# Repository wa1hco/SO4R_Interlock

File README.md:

# SO4R_Interlock V2
The interlock manages up to 4 radios for a contesting scenario

Baseline capability for one SSB/CW radio plus 3 WSJTX radios.
Isolation is sufficient to allow reception on three radios when one radio is transmitting.
SSB/CW radio usually has a rotatable antenna. The three WSJTx instances have radio and antenna, usually a fixed direction.  
Amplifier is shared among radios.

WSJTX feeds N1MM, Gridtracker or other program that display a combined list of stations needed from three radios.
Operator clicks on a station in the list and that WSJTX begins the contact.
SSB/CW operator can continue to operate, which interrupts WSJTX transmission.

Each of 4 radios have a priority with SSB/CW being highest.
SSB/CW operation can continue while WSJTX is making contacts while staying within the ARRL VHF contest rules because WSJTX transmission is interrupted when SSB/CW transmits.

When a higher priority tranmitter needs to interrupt a lower priority tranmission, 
the interlock gates the PTT line to the lower priority radio.  This keeps the radio's
built in sequencer operating to protect the amplifier, preamp, and relays.  
The interlock also controls the RF relays to disconnect the lower priority transmitter 
and connect the highest priority transmitter

Radio Interface
* PTT, output open collector, low true, 60V, 300 mA
* KEY, input, open collector, low true, 5 to 15 V
* CAT, bidirectional, open collector, ttl levels, serial communication
* Spare, direct connection to MCU I/O pin

Relay interface
* Relay output are drive high from nominal 12V source
  * Uses BTS5200-4 driver chip for fault protection and diagnositc capability
* 12V is sourced from a rig interface using a standard coaxial type M connector
* Each output drives dual 4:1 mux boards with added relay for isolation

USB serial interface
* Implemented with FTDI FT230 usb serial chip
* RTS, output, for signaling Transmit, connected to radio PTT
* CTS, input, available, interfaced to MCU, no function assigned
* Serial TxD, RxD, for CAT, optional growth provision
* FT230 USB EEPROM changed to make it easier to find the ports when connected to a computer
  * Manufacturer string is "FTDI WA1HCO"
  * Product string is "FT230X SO4R Port {1-4}"

SSB/CW radio interface
* highest priority radio, Priority = 1
* USB serial TxD, RxD used for MCU programming
* USB serial RTS used for keying radio from N1MM
* KEY signal from Radio used to set priority and control relays

WSJTX radio interface
* Lower priority radios, Priority = 2, 3, or 4
* USB serial implements COM port, control signal RTS used by WSJTX software
* Serial data TxD and RxD converted to CAT bidirectional open collector, growth provision
* RTS signal used for PTT command to radio
* CTS signal routed to MCU but not assigned a function

WSJTX operation
* Operator uses ssb/cw radio for contacts and has highest priority for transmitting.
* 3 WSJTX instances listen on 3 radios in 3 directions.
* Each WSJTX sends it list of callsigns to N1MM or Gridtracker which displays list of stations color coded by log status (needed or duplicate).
* The operator clicks on a callsign in the list to start a WSJTX contact.
* WSJTX indicates need to transmit by asserting RTS on its serial interface

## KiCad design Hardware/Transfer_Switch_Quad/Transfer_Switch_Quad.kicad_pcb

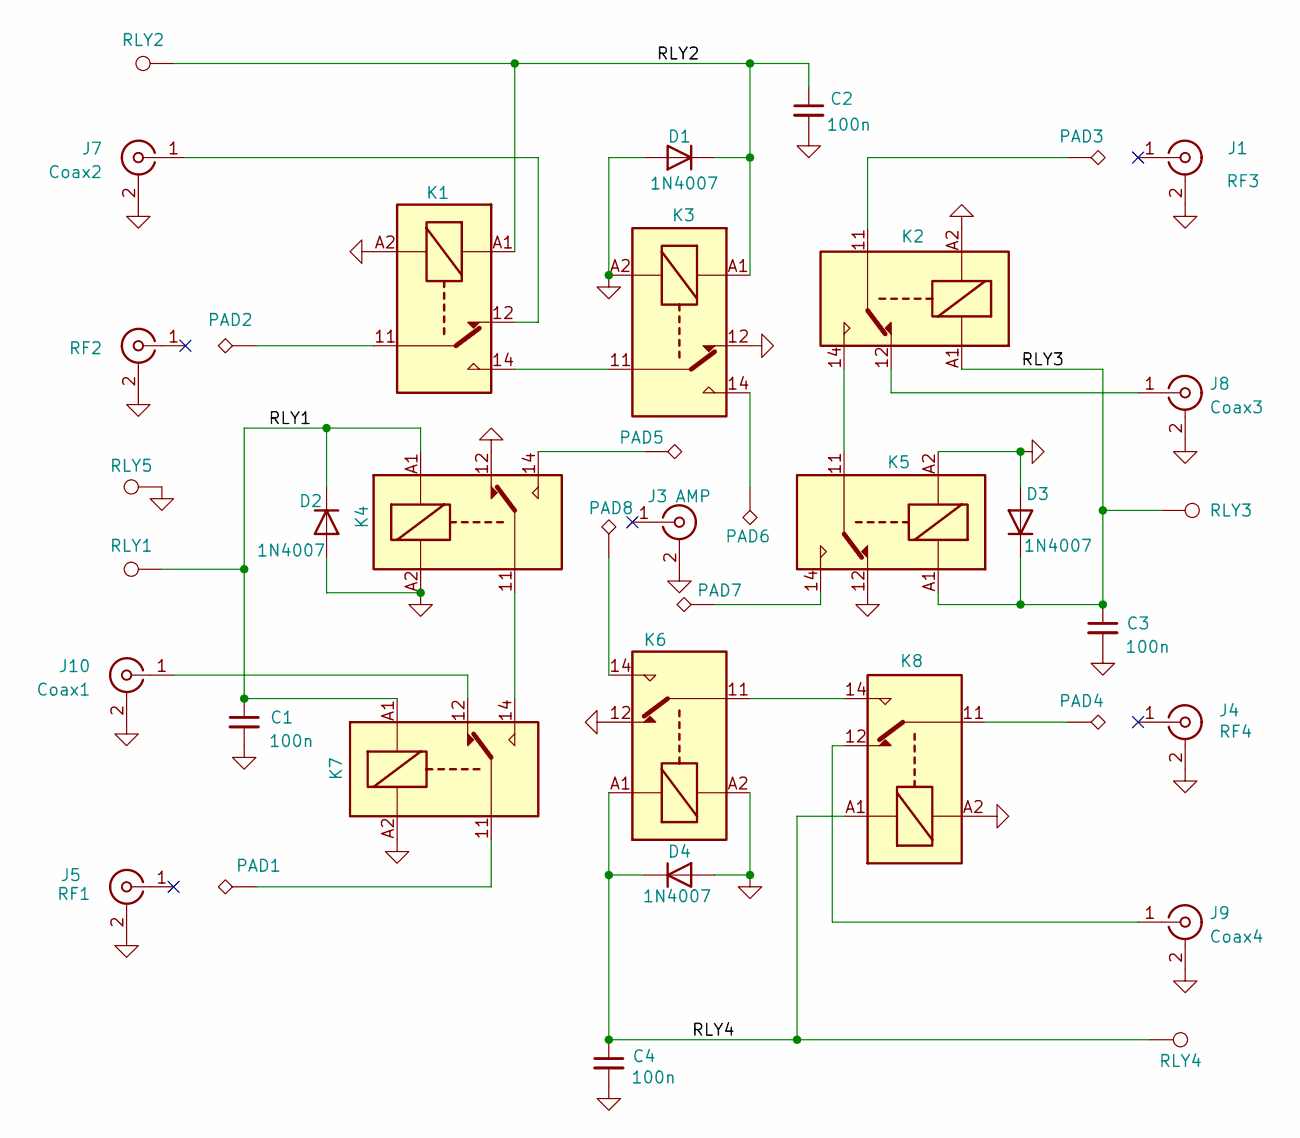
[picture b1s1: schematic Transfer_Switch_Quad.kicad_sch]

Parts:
C1, C2, C3, C4: 100n; C_0805_2012Metric
D1, D2, D3, D4: 1N4007; D_SMA
J1: RF3; UHF_SO-239_hole
J2: RF2; UHF_SO-239_hole
J3: AMP; UHF_SO-239_hole
J4: RF4; UHF_SO-239_hole
J5: RF1; UHF_SO-239_hole
J7: Coax2; SMA_Amphenol_901-144_Vertical
J8: Coax3; SMA_Amphenol_901-144_Vertical
J9: Coax4; SMA_Amphenol_901-144_Vertical
J10: Coax1; SMA_Amphenol_901-144_Vertical
K1, K2, K3, K4, K5, K6, K7, K8: G2RL-1-E; Relay_SPDT_Omron_G2RL-1-E
PAD1, PAD2, PAD3, PAD4, PAD5, PAD6, PAD7, PAD8: PAD2X4; SolderWirePad_1x01_SMD_2x4mm
RLY1, RLY2, RLY3, RLY4, RLY5: SolderWire-0.25sqmm_1x01_D0.65mm_OD2mm

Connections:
/RLY1: C1.1, D2.1 (K), K4.A1, K7.A1, RLY1.1
/RLY2: C2.1, D1.1 (K), K1.A1, K3.A1, RLY2.1
/RLY3: C3.1, D3.1 (K), K2.A1, K5.A1, RLY3.1
/RLY4: C4.1, D4.1 (K), K6.A1, K8.A1, RLY4.1
GND: C1.2, C2.2, C3.2, C4.2, D1.2 (A), D2.2 (A), D3.2 (A), D4.2 (A), J1.2 (Ext), J2.2 (Ext), J3.2 (Ext), J4.2 (Ext), J5.2 (Ext), J7.2 (Ext), J8.2 (Ext), J9.2 (Ext), J10.2 (Ext), K1.A2, K2.A2, K3.12, K3.A2, K4.12, K4.A2, K5.12, K5.A2, K6.12, K6.A2, K7.A2, K8.A2, RLY5.1
unnamed: J7.1 (In), K1.12
unnamed: J8.1 (In), K2.12
unnamed: J9.1 (In), K8.12
unnamed: J10.1 (In), K7.12
unnamed: K1.11, PAD2.1
unnamed: K1.14, K3.11
unnamed: K2.11, PAD3.1
unnamed: K2.14, K5.11
unnamed: K3.14, PAD6.1
unnamed: K4.11, K7.14
unnamed: K4.14, PAD5.1
unnamed: K5.14, PAD7.1
unnamed: K6.11, K8.14
unnamed: K6.14, PAD8.1
unnamed: K7.11, PAD1.1
unnamed: K8.11, PAD4.1

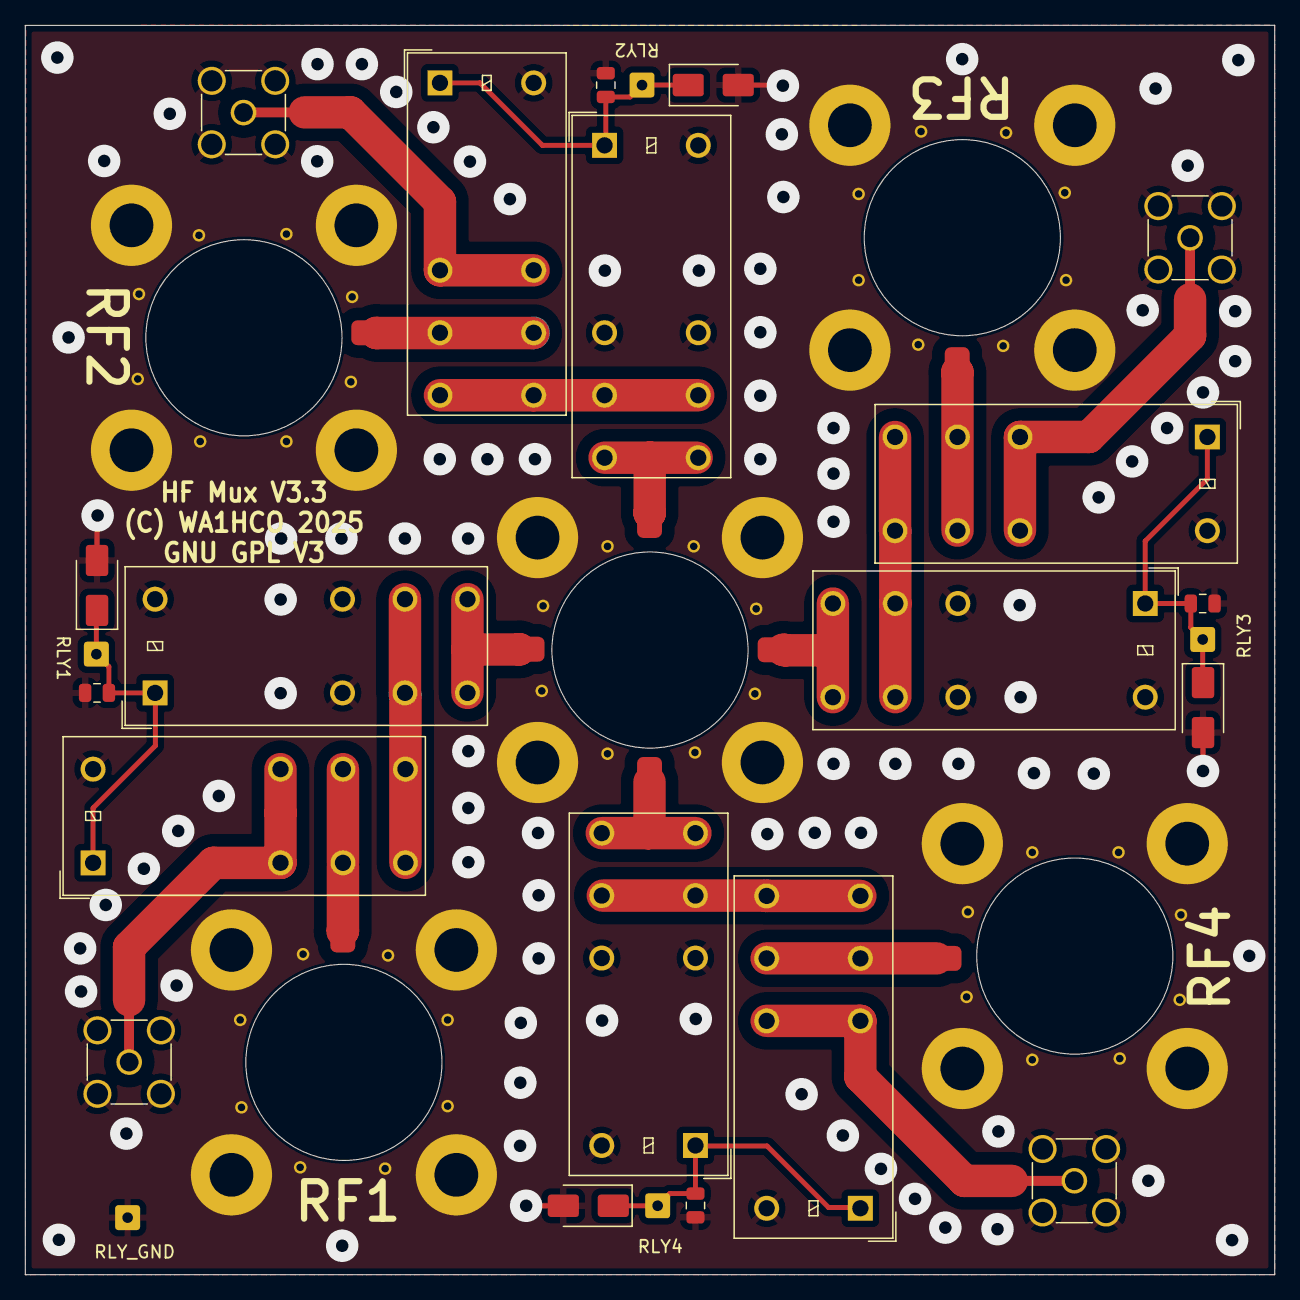
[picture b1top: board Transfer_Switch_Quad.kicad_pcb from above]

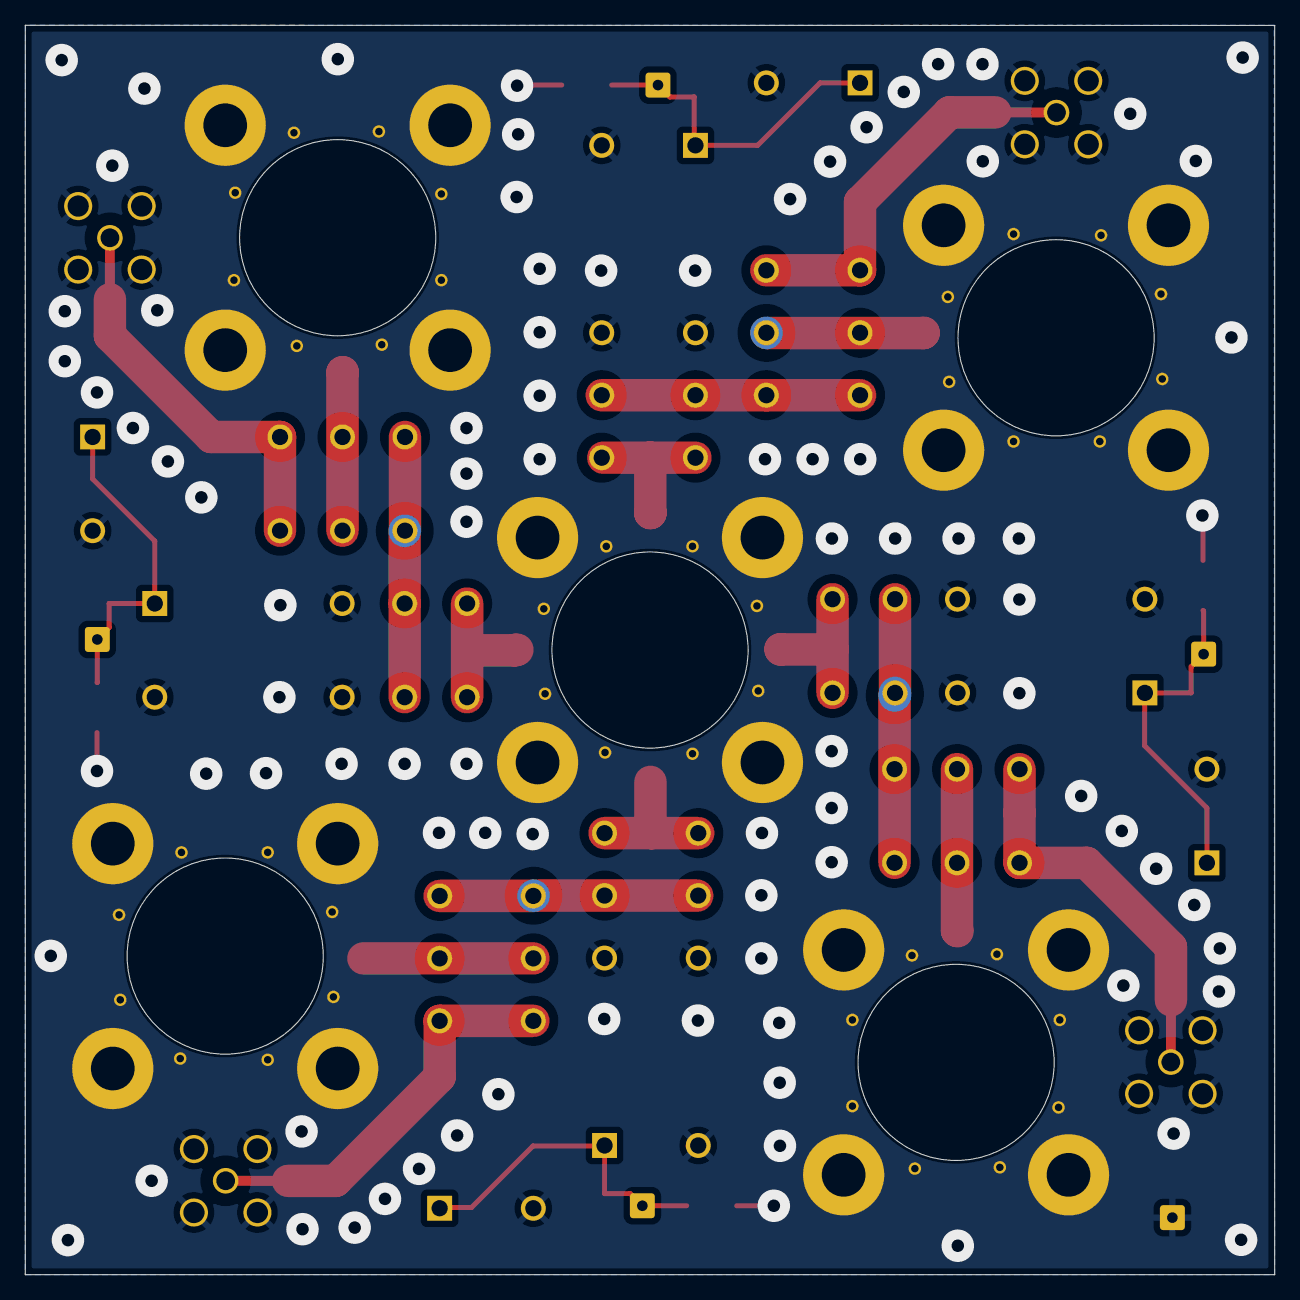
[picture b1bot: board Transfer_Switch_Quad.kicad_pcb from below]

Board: 2 copper layers, 100.0 x 100.0 mm, 38 parts (5 on the bottom side), 21 nets.

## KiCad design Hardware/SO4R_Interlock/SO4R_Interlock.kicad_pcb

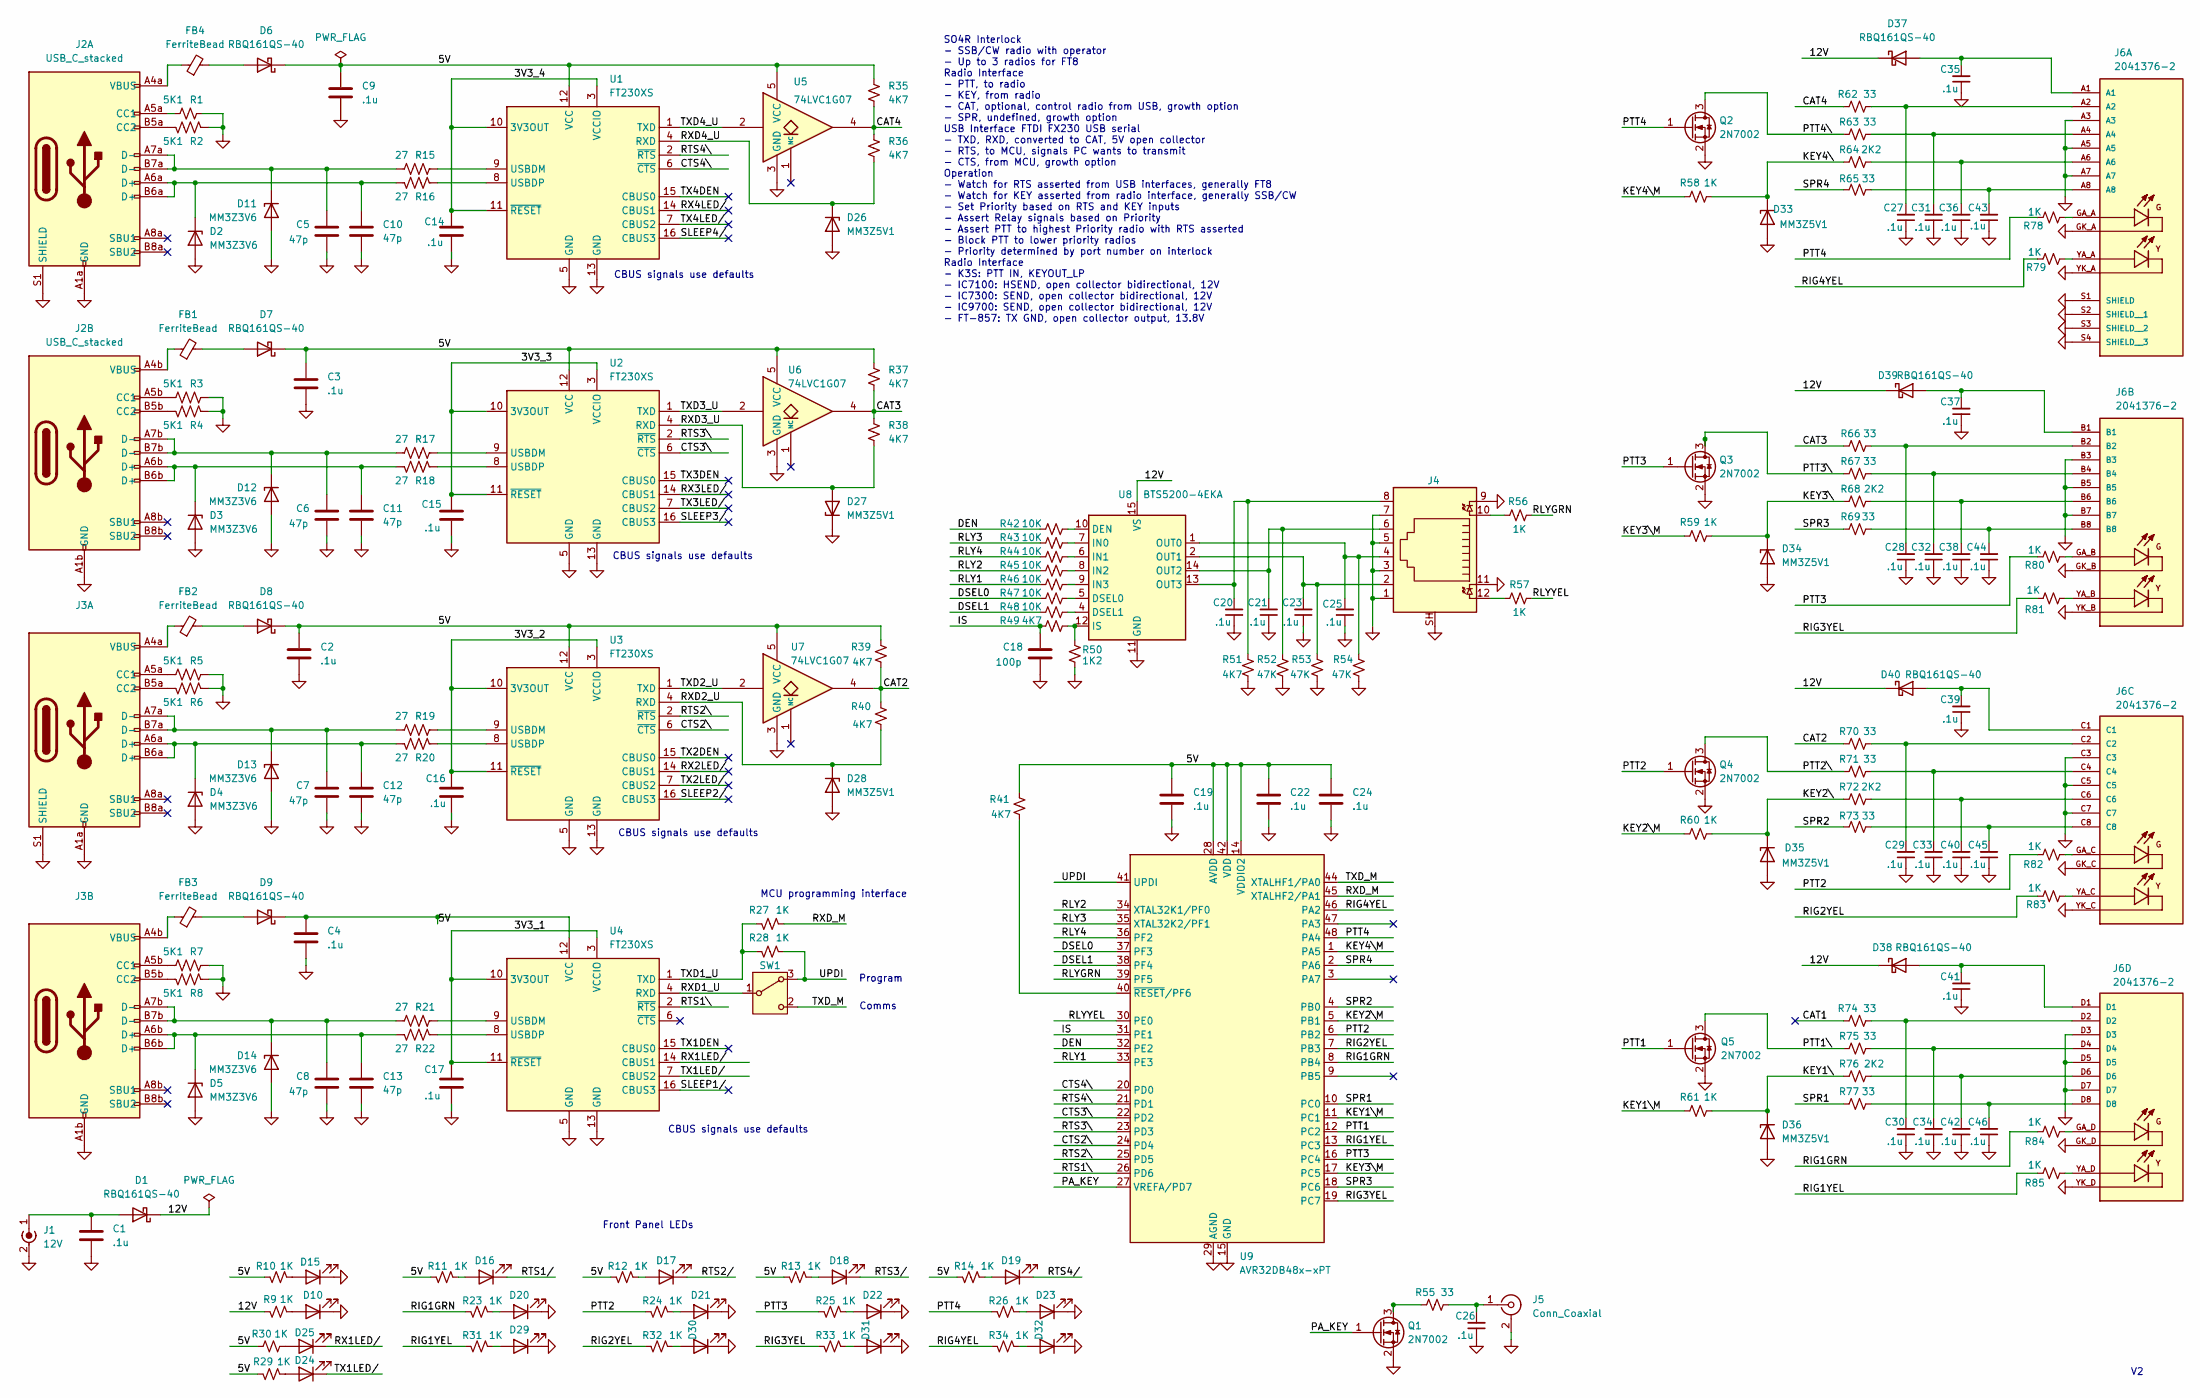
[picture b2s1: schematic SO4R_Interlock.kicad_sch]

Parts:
C1, C2, C3, C4, C9, C14, C15, C16, C17, C19, C22, C24: .1u; C_0402_1005Metric; LCSC PN C15849
C5, C6, C7, C8, C10, C11, C12, C13: 47p; C_0402_1005Metric; LCSC PN C1671
C18: 100p; C_0402_1005Metric; LCSC PN C1671
C20, C21, C23, C25, C26, C27, C28, C29, C30, C31, C32, C33, C34, C35, C36, C37, C38, C39, C40, C41, C42, C43, C44, C45, C46: .1u; C_0402_1005Metric
D1, D6, D7, D8, D9, D37, D38, D39, D40: RBQ161QS-40; D_0402_1005Metric
D2, D3, D4, D5, D11, D12, D13, D14: MM3Z3V6; D_SOD-523; LCSC PN C19077454
D10, D15: Green; LED_0603_1608Metric; LCSC PN C22371299
D16, D17, D18, D19, D20, D21, D22, D23, D29, D30, D31, D32: Green; LED_0805_2012Metric; LCSC PN C22371299
D24, D25: Yellow; LED_0603_1608Metric; LCSC PN C72038
D26, D27, D28: MM3Z5V1; D_SOD-323F
D33, D34, D35, D36: MM3Z5V1; D_SOD-523; LCSC C116949
FB1, FB2, FB3, FB4: FerriteBead; L_0805_2012Metric; LCSC PN C1017
J1: 12V; BarrelJack_Kycon_KLDX-0202-xC_Horizontal
J2: USB_C_stacked; CU3616SASCLA004-LF
J3: CU3616SASCLA004-LF
J4: RJ45_LED_Shielded; RJ45_Amphenol_RJHSE538X
J5: Conn_Coaxial; KLPX-0848A-2-B_KYC
J6: 2041376-2; TE_2041376-2; PARTREV B
Q1, Q2, Q3, Q4, Q5: 2N7002; SOT-23
R1, R2, R3, R4, R5, R6, R7, R8: 5K1; R_0402_1005Metric; LCSC PN C23186
R9, R10, R11, R12, R13, R14, R23, R24, R25, R26, R27, R28, R29, R30, R31, R32, R33, R34: 1K; R_0402_1005Metric; LCSC PN C21190
R15, R16, R17, R18, R19, R20, R21, R22: 27; R_0402_1005Metric; LCSC PN C25190
R35, R36, R37, R38, R39, R40, R41, R49, R51: 4K7; R_0402_1005Metric
R42, R43, R44, R45, R46, R47, R48: 10K; R_0402_1005Metric
R50: 1K2; R_0402_1005Metric
R52, R53, R54: 47K; R_0402_1005Metric
R55, R62, R63, R65, R66, R67, R69, R70, R71, R73, R74, R75, R77: 33; R_0402_1005Metric
R56, R57, R78, R79, R80, R81, R82, R83, R84, R85: 1K; R_0402_1005Metric
R58, R59, R60, R61: 1K; R_0402_1005Metric; LCSC C21190
R64, R68, R72, R76: 2K2; R_0402_1005Metric; LCSC C113303
SW1: SW_Wuerth_450301014042; SW_Slide-03_Wuerth-WS-SLTV_10x2.5x6.4_P2.54mm
U1, U2, U3, U4: FT230XS; SSOP-16_3.9x4.9mm_P0.635mm; LCSC PN C69082
U5, U6, U7: 74LVC1G07; SOT-23-5
U8: BTS5200-4EKA; Infineon_PG-DSO-14-48
U9: AVR32DB48x-xPT; TQFP-48_7x7mm_P0.5mm

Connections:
/3V3_1: C17.1, U4.3 (VCCIO), U4.10 (3V3OUT), U4.11 (~RESET)
/3V3_2: C16.1, U3.3 (VCCIO), U3.10 (3V3OUT), U3.11 (~RESET)
/3V3_3: C15.1, U2.3 (VCCIO), U2.10 (3V3OUT), U2.11 (~RESET)
/3V3_4: C14.1, U1.3 (VCCIO), U1.10 (3V3OUT), U1.11 (~RESET)
/5V: C2.1, C3.1, C4.1, C9.1, C19.1, C22.1, C24.1, D6.1 (K), D7.1 (K), D8.1 (K), D9.1 (K), R10.2, R11.1, R12.1, R13.1, R14.1, R29.2, R30.2, R35.1, R37.1, R39.1, R41.1, U1.12 (VCC), U2.12 (VCC), U3.12 (VCC), U4.12 (VCC), U5.5 (VCC), U6.5 (VCC), U7.5 (VCC), U9.14 (VDDIO2), U9.28 (AVDD), U9.42 (VDD)
/12V: D1.1 (K), D37.1 (K), D38.1 (K), D39.1 (K), D40.1 (K), R9.2, U8.15 (VS)
/CAT1: R74.1
/CAT2: R39.2, R40.1, R70.1, U7.4
/CAT3: R37.2, R38.1, R66.1, U6.4
/CAT4: R35.2, R36.1, R62.1, U5.4
/CTS2\: U3.6 (~CTS), U9.24 (PD4)
/CTS3\: U2.6 (~CTS), U9.22 (PD2)
/CTS4\: U1.6 (~CTS), U9.20 (PD0)
/DEN: R42.1, U9.32 (PE2)
/DSEL0: R47.1, U9.37 (PF3)
/DSEL1: R48.1, U9.38 (PF4)
/IS: C18.1, R49.1, U9.31 (PE1)
/KEY1\: D36.1 (K), R61.1, R76.2
/KEY1\M: R61.2, U9.11 (PC1)
/KEY2\: D35.1 (K), R60.1, R72.2
/KEY2\M: R60.2, U9.5 (PB1)
/KEY3\: D34.1 (K), R59.1, R68.2
/KEY3\M: R59.2, U9.17 (PC5)
/KEY4\: D33.1 (K), R58.1, R64.2
/KEY4\M: R58.2, U9.1 (PA5)
/PA_KEY: Q1.1 (G), U9.27 (VREFA/PD7)
/PTT1: Q5.1 (G), U9.12 (PC2)
/PTT1\: Q5.3 (D), R75.1
/PTT2: Q4.1 (G), R24.1, R82.2, U9.6 (PB2)
/PTT2\: Q4.3 (D), R71.1
/PTT3: Q3.1 (G), R25.1, R80.2, U9.16 (PC4)
/PTT3\: Q3.3 (D), R67.1
/PTT4: Q2.1 (G), R26.1, R78.2, U9.48 (PA4)
/PTT4\: Q2.3 (D), R63.1
/RIG1GRN: R23.1, R84.2, U9.8 (PB4)
/RIG1YEL: R31.1, R85.2, U9.13 (PC3)
/RIG2YEL: R32.1, R83.2, U9.7 (PB3)
/RIG3YEL: R33.1, R81.2, U9.19 (PC7)
/RIG4YEL: R34.1, R79.2, U9.46 (PA2)
/RLY1: R46.1, U9.33 (PE3)
/RLY2: R45.1, U9.34 (XTAL32K1/PF0)
/RLY3: R43.1, U9.35 (XTAL32K2/PF1)
/RLY4: R44.1, U9.36 (PF2)
/RLYGRN: R56.2, U9.39 (PF5)
/RLYYEL: R57.2, U9.30 (PE0)
/RTS1\: U4.2 (~RTS), U9.26 (PD6)
/RTS1/: D16.1 (K)
/RTS2\: U3.2 (~RTS), U9.25 (PD5)
/RTS2/: D17.1 (K)
/RTS3\: U2.2 (~RTS), U9.23 (PD3)
/RTS3/: D18.1 (K)
/RTS4\: U1.2 (~RTS), U9.21 (PD1)
/RTS4/: D19.1 (K)
/RX1LED/: D25.1 (K), U4.14 (CBUS1)
/RX2LED/: U3.14 (CBUS1)
/RX3LED/: U2.14 (CBUS1)
/RX4LED/: U1.14 (CBUS1)
/RXD1_U: SW1.1 (B), U4.4 (RXD)
/RXD2_U: D28.1 (K), R40.2, U3.4 (RXD)
/RXD3_U: D27.2 (A), R38.2, U2.4 (RXD)
/RXD4_U: D26.1 (K), R36.2, U1.4 (RXD)
/RXD_M: R27.2, U9.45 (XTALHF2/PA1)
/SLEEP1/: U4.16 (CBUS3)
/SLEEP2/: U3.16 (CBUS3)
/SLEEP3/: U2.16 (CBUS3)
/SLEEP4/: U1.16 (CBUS3)
/SPR1: R77.1, U9.10 (PC0)
/SPR2: R73.1, U9.4 (PB0)
/SPR3: R69.1, U9.18 (PC6)
/SPR4: R65.1, U9.2 (PA6)
/TX1DEN: U4.15 (CBUS0)
/TX1LED/: D24.1 (K), U4.7 (CBUS2)
/TX2DEN: U3.15 (CBUS0)
/TX2LED/: U3.7 (CBUS2)
/TX3DEN: U2.15 (CBUS0)
/TX3LED/: U2.7 (CBUS2)
/TX4DEN: U1.15 (CBUS0)
/TX4LED/: U1.7 (CBUS2)
/TXD1_U: R27.1, R28.1, U4.1 (TXD)
/TXD2_U: U3.1 (TXD), U7.2
/TXD3_U: U2.1 (TXD), U6.2
/TXD4_U: U1.1 (TXD), U5.2
/TXD_M: SW1.2 (C), U9.44 (XTALHF1/PA0)
/UPDI: R28.2, SW1.3 (A), U9.41 (UPDI)
GND: C1.2, C2.2, C3.2, C4.2, C5.2, C6.2, C7.2, C8.2, C9.2, C10.2, C11.2, C12.2, C13.2, C14.2, C15.2, C16.2, C17.2, C18.2, C19.2, C20.1, C21.1, C22.2, C23.1, C24.2, C25.1, C26.1, C27.1, C28.1, C29.1, C30.1, C31.1, C32.1, C33.1, C34.1, C35.1, C36.1, C37.1, C38.1, C39.1, C40.1, C41.1, C42.1, C43.1, C44.1, C45.1, C46.1, D2.2 (A), D3.2 (A), D4.2 (A), D5.2 (A), D10.1 (K), D11.2 (A), D12.2 (A), D13.2 (A), D14.2 (A), D15.1 (K), D20.1 (K), D21.1 (K), D22.1 (K), D23.1 (K), D26.2 (A), D27.1 (K), D28.2 (A), D29.1 (K), D30.1 (K), D31.1 (K), D32.1 (K), D33.2 (A), D34.2 (A), D35.2 (A), D36.2 (A), J1.2 (Ext), J2.A1a (GND), J2.A1b (GND), J2.A12a (GND), J2.A12b (GND), J2.B1a (GND), J2.B1b (GND), J2.B12a (GND), J2.B12b (GND), J2.S1 (SHIELD), J3.A1a (GND), J3.A1b (GND), J3.A12a (GND), J3.A12b (GND), J3.B1a (GND), J3.B1b (GND), J3.B12a (GND), J3.B12b (GND), J3.S1 (SHIELD), J4.1, J4.3, J4.5, J4.7, J4.9, J4.11, J4.SH, J5.2 (Ext), J6.A3, J6.A5, J6.A7, J6.B3, J6.B5, J6.B7, J6.C3, J6.C5, J6.C7, J6.D3, J6.D5, J6.D7, J6.GK_A, J6.GK_B, J6.GK_C, J6.GK_D, J6.S1 (SHIELD), J6.S2 (SHIELD__1), J6.S3 (SHIELD__2), J6.S4 (SHIELD__3), J6.YK_A, J6.YK_B, J6.YK_C, J6.YK_D, Q1.2 (S), Q2.2 (S), Q3.2 (S), Q4.2 (S), Q5.2 (S), R1.1, R2.1, R3.1, R4.1, R5.1, R6.1, R7.1, R8.1, R50.2, R51.2, R52.2, R53.2, R54.2, U1.5 (GND), U1.13 (GND), U2.5 (GND), U2.13 (GND), U3.5 (GND), U3.13 (GND), U4.5 (GND), U4.13 (GND), U5.3 (GND), U6.3 (GND), U7.3 (GND), U8.11 (GND), U9.15 (GND), U9.29 (AGND), U9.43 (GND)
unnamed: C27.2, J6.A2, R62.2
unnamed: C28.2, J6.B2, R66.2
unnamed: C29.2, J6.C2, R70.2
unnamed: C30.2, J6.D2, R74.2
unnamed: C31.2, J6.A4, R63.2
unnamed: C32.2, J6.B4, R67.2
unnamed: C33.2, J6.C4, R71.2
unnamed: C34.2, J6.D4, R75.2
unnamed: C36.2, J6.A6, R64.1
unnamed: C38.2, J6.B6, R68.1
unnamed: C40.2, J6.C6, R72.1
unnamed: C42.2, J6.D6, R76.1
unnamed: C43.2, J6.A8, R65.2
unnamed: C44.2, J6.B8, R69.2
unnamed: C45.2, J6.C8, R73.2
unnamed: C46.2, J6.D8, R77.2
unnamed: C1.1, D1.2 (A), J1.1 (In)
unnamed: C10.1, D2.1 (K), J2.A6a (D+), J2.B6a (D+), R16.2
unnamed: C11.1, D3.1 (K), J2.A6b (D+), J2.B6b (D+), R18.2
unnamed: C12.1, D4.1 (K), J3.A6a (D+), J3.B6a (D+), R20.2
unnamed: C13.1, D5.1 (K), J3.A6b (D+), J3.B6b (D+), R22.2
unnamed: D6.2 (A), FB4.2
unnamed: D7.2 (A), FB1.2
unnamed: D8.2 (A), FB2.2
unnamed: D9.2 (A), FB3.2
unnamed: D10.2 (A), R9.1
unnamed: C5.1, D11.1 (K), J2.A7a (D-), J2.B7a (D-), R15.2
unnamed: C6.1, D12.1 (K), J2.A7b (D-), J2.B7b (D-), R17.2
unnamed: C7.1, D13.1 (K), J3.A7a (D-), J3.B7a (D-), R19.2
unnamed: C8.1, D14.1 (K), J3.A7b (D-), J3.B7b (D-), R21.2
unnamed: D15.2 (A), R10.1
unnamed: D16.2 (A), R11.2
unnamed: D17.2 (A), R12.2
unnamed: D18.2 (A), R13.2
unnamed: D19.2 (A), R14.2
unnamed: D20.2 (A), R23.2
unnamed: D21.2 (A), R24.2
unnamed: D22.2 (A), R25.2
unnamed: D23.2 (A), R26.2
unnamed: D24.2 (A), R29.1
unnamed: D25.2 (A), R30.1
unnamed: D29.2 (A), R31.2
unnamed: D30.2 (A), R32.2
unnamed: D31.2 (A), R33.2
unnamed: D32.2 (A), R34.2
unnamed: C35.2, D37.2 (A), J6.A1
unnamed: C41.2, D38.2 (A), J6.D1
unnamed: C37.2, D39.2 (A), J6.B1
unnamed: C39.2, D40.2 (A), J6.C1
unnamed: FB1.1, J2.A4b (VBUS), J2.A9b (VBUS), J2.B4b (VBUS), J2.B9b (VBUS)
unnamed: FB2.1, J3.A4a (VBUS), J3.A9a (VBUS), J3.B4a (VBUS), J3.B9a (VBUS)
unnamed: FB3.1, J3.A4b (VBUS), J3.A9b (VBUS), J3.B4b (VBUS), J3.B9b (VBUS)
unnamed: FB4.1, J2.A4a (VBUS), J2.A9a (VBUS), J2.B4a (VBUS), J2.B9a (VBUS)
unnamed: J2.A5a (CC1), R1.2
unnamed: J2.B5a (CC2), R2.2
unnamed: J2.A5b (CC1), R3.2
unnamed: J2.B5b (CC2), R4.2
unnamed: J3.A5a (CC1), R5.2
unnamed: J3.B5a (CC2), R6.2
unnamed: J3.A5b (CC1), R7.2
unnamed: J3.B5b (CC2), R8.2
unnamed: J4.10, R56.1
unnamed: J4.12, R57.1
unnamed: C26.2, J5.1 (In), R55.2
unnamed: J6.GA_A, R78.1
unnamed: J6.GA_B, R80.1
unnamed: J6.GA_C, R82.1
unnamed: J6.GA_D, R84.1
unnamed: J6.YA_A, R79.1
unnamed: J6.YA_B, R81.1
unnamed: J6.YA_C, R83.1
unnamed: J6.YA_D, R85.1
unnamed: Q1.3 (D), R55.1
unnamed: R15.1, U1.9 (USBDM)
unnamed: R16.1, U1.8 (USBDP)
unnamed: R17.1, U2.9 (USBDM)
unnamed: R18.1, U2.8 (USBDP)
unnamed: R19.1, U3.9 (USBDM)
unnamed: R20.1, U3.8 (USBDP)
unnamed: R21.1, U4.9 (USBDM)
unnamed: R22.1, U4.8 (USBDP)
unnamed: R42.2, U8.10 (DEN)
unnamed: R47.2, U8.5 (DSEL0)
unnamed: R48.2, U8.4 (DSEL1)
unnamed: R43.2, U8.7 (IN0)
unnamed: R44.2, U8.6 (IN1)
unnamed: R45.2, U8.8 (IN2)
unnamed: R46.2, U8.9 (IN3)
unnamed: R49.2, R50.1, U8.12 (IS)
unnamed: C25.2, J4.4, R54.1, U8.1 (OUT0)
unnamed: C23.2, J4.2, R53.1, U8.2 (OUT1)
unnamed: C21.2, J4.6, R52.1, U8.14 (OUT2)
unnamed: C20.2, J4.8, R51.1, U8.13 (OUT3)
unnamed: R41.2, U9.40 (~RESET/PF6)

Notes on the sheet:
SO4R Interlock - SSB/CW radio with operator - Up to 3 radios for FT8 Radio Interface - PTT, to radio - KEY, from radio - CAT, optional, control radio from USB, growth option - SPR, undefined, growth option USB Interface FTDI FX230 USB serial - TXD, RXD, converted to CAT, 5V open collector - RTS, to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
CBUS signals use defaults
Program
MCU programming interface
Front Panel LEDs
Comms

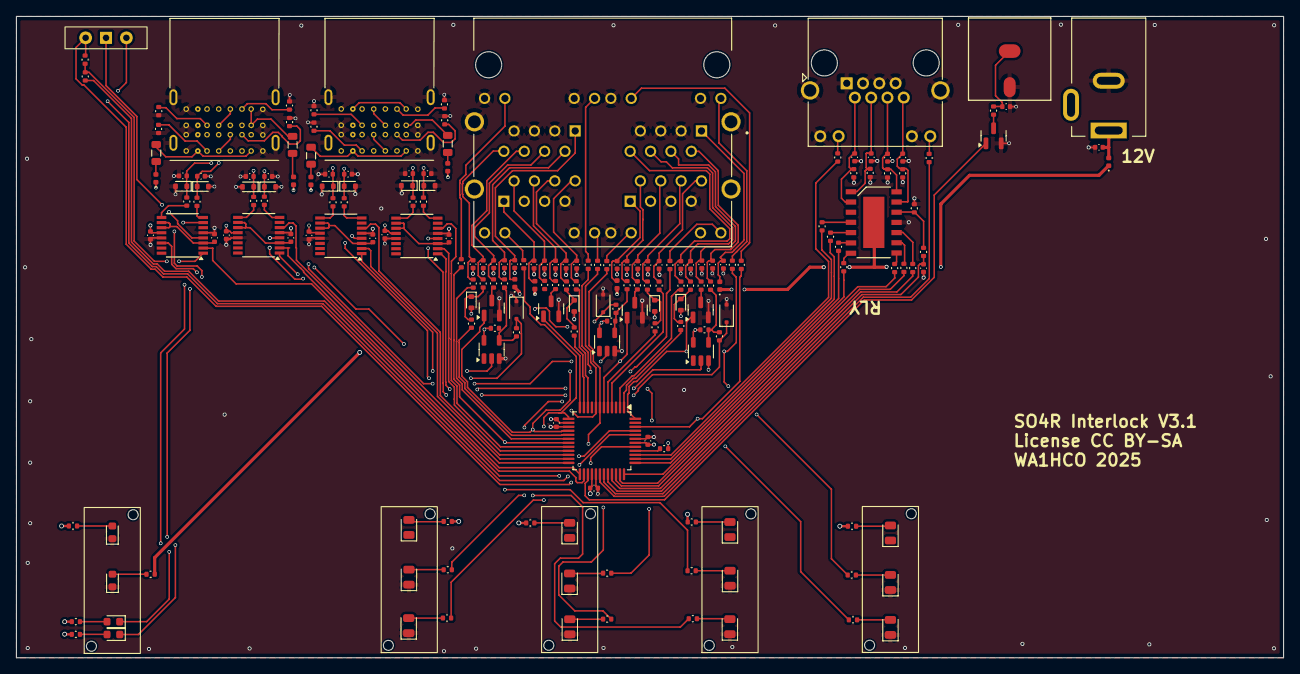
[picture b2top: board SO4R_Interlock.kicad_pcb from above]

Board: 4 copper layers, 158.0 x 80.0 mm, 196 parts (0 on the bottom side), 160 nets.

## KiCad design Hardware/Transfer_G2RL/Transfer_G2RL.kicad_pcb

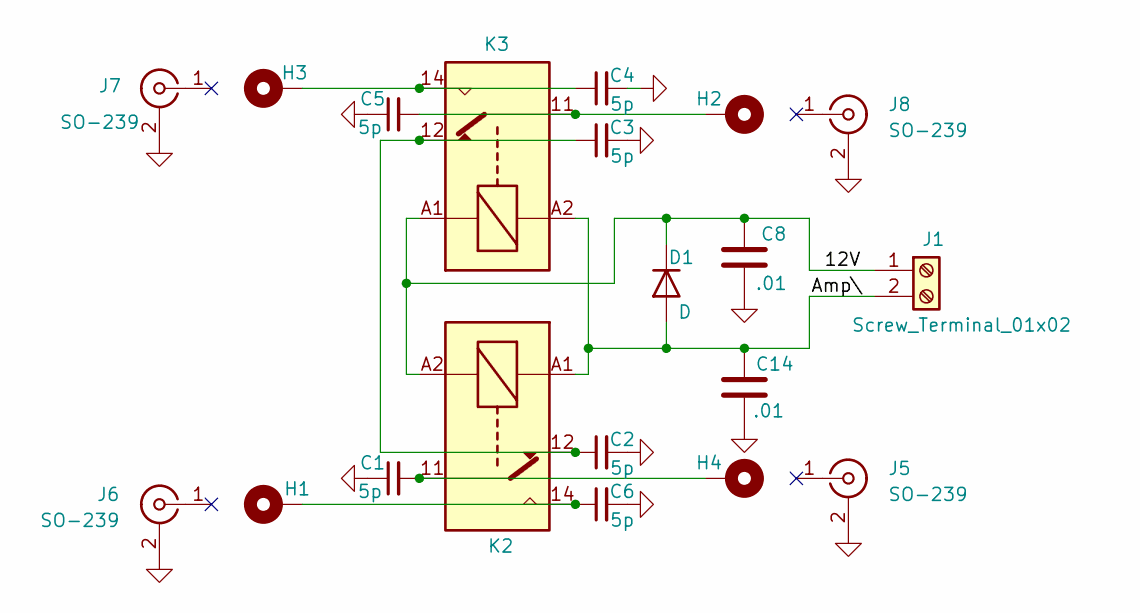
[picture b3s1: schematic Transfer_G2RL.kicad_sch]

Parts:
C1, C2, C3, C4, C5, C6: 5p; C_0805_2012Metric
C8, C14: .01; C_0805_2012Metric
D1: D; D_SOD-323
H1, H2, H3, H4: MountingHole_Pad; TestPoint_Plated_Hole_D2.0mm
J1: Screw_Terminal_01x02; TerminalBlock_TE_282834-2_1x02_P2.54mm_Horizontal
J5, J6, J7, J8: SO-239; UHF_SO-239
K2, K3: G2RL-1-E; Relay_SPDT_Omron_G2RL-1-E

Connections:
/12V: C8.1, D1.1 (K), J1.1, K2.A2, K3.A1
/Amp\: C14.1, D1.2 (A), J1.2, K2.A1, K3.A2
GND: C1.1, C2.2, C3.2, C4.2, C5.1, C6.2, C8.2, C14.2, J5.2 (Ext), J6.2 (Ext), J7.2 (Ext), J8.2 (Ext)
unnamed: C1.2, H4.1, K2.11
unnamed: C2.1, C3.1, K2.12, K3.12
unnamed: C4.1, H3.1, K3.14
unnamed: C5.2, H2.1, K3.11
unnamed: C6.1, H1.1, K2.14

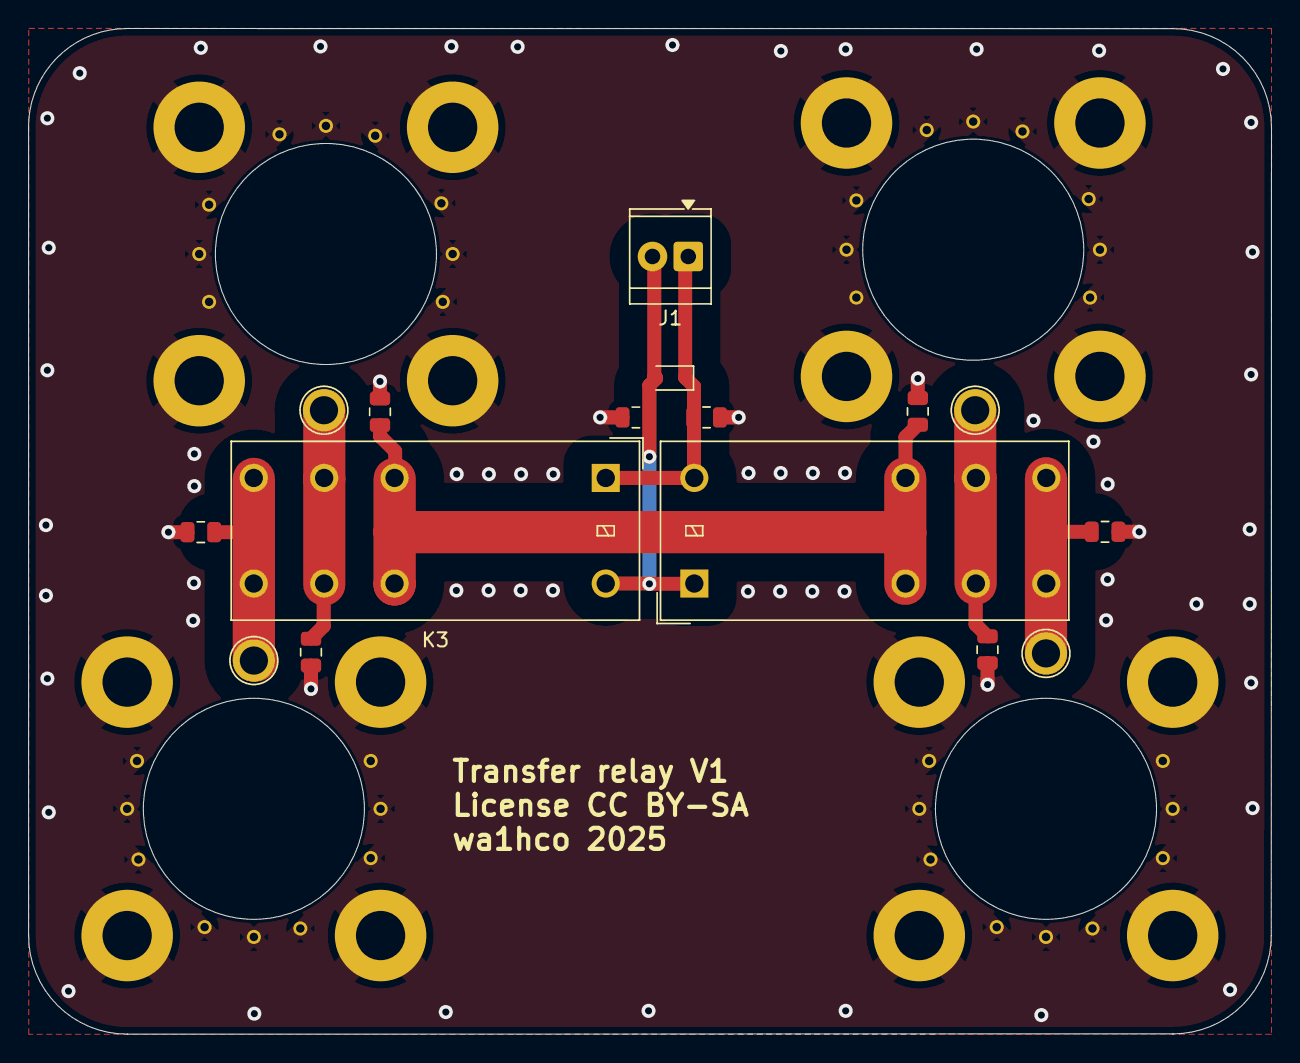
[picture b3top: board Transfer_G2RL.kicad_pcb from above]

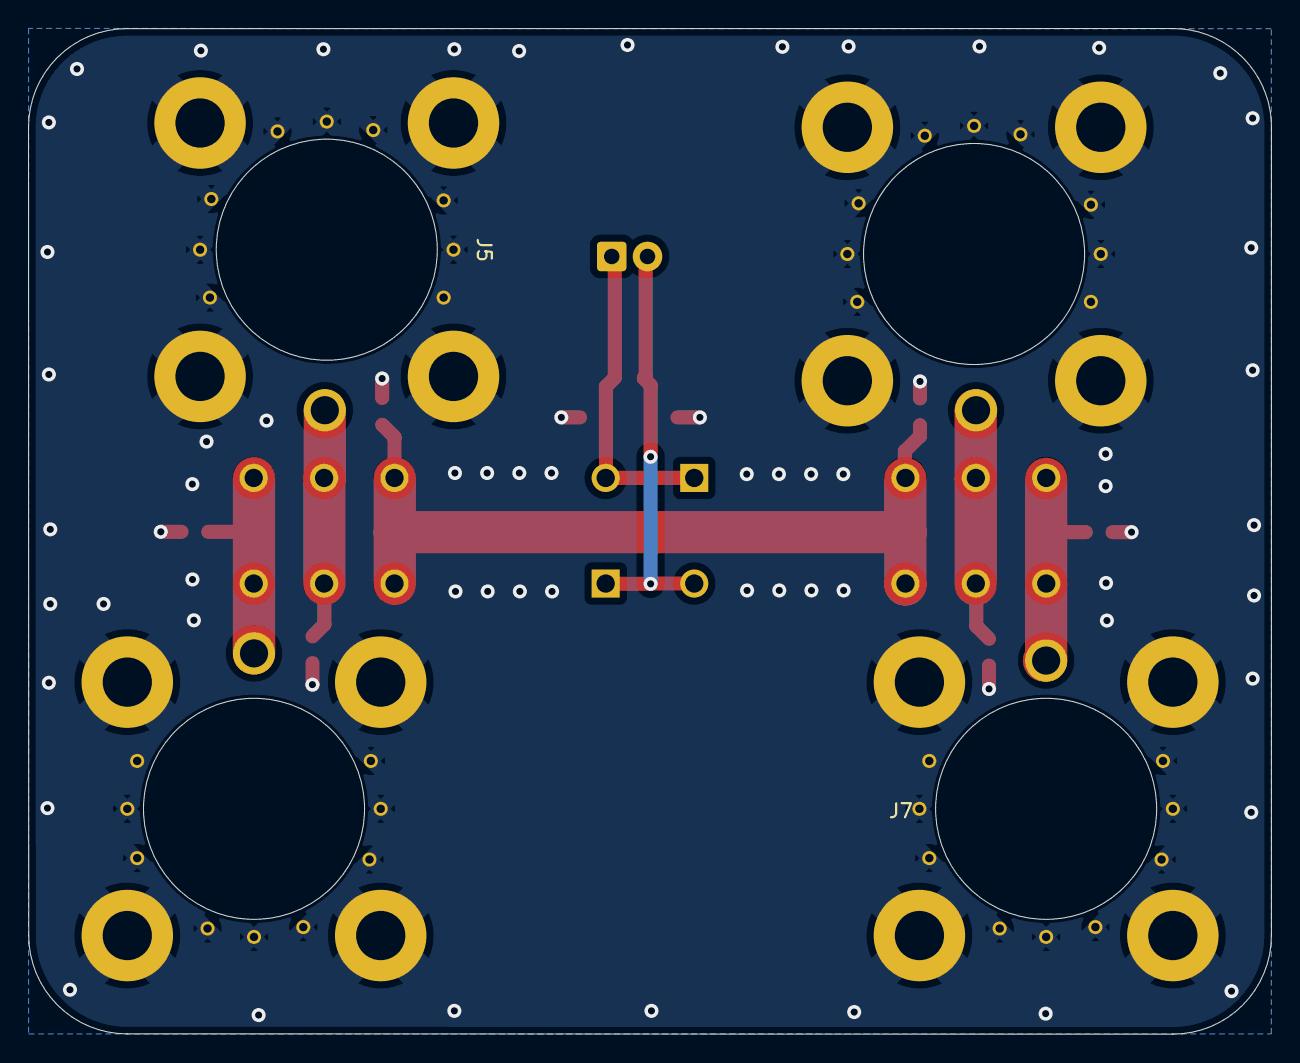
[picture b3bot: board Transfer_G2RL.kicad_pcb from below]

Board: 2 copper layers, 88.3 x 71.4 mm, 20 parts (4 on the bottom side), 8 nets.

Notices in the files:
Hardware/SO4R_Interlock/SO4R_Interlock.kicad_pcb:
License CC BY-SA
Hardware/Transfer_Switch_Quad/Transfer_Switch_Quad.kicad_pcb:
GNU GPL V3
